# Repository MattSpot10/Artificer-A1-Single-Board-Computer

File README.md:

# Artificer A1 Single Board Computer
 An open source single board computer with AI capabilities. (Still in progress)

### **Features/Capabilites
- Alliwnner T527 SoC (Octa-core ARM Cortex-A55, up to 1.8 GHz)
- 4GB LPDDR4 SDRAM
- Dual Gigibit Ethernet (RJ45 ports capable of PoE)
- PCIe gen 2.1
- Display Port, HDMI, 2x4 lane MIPI DSI
- 4x2 lane MIPI CSI
- SD Card as boot media
- M8800DS2 Wifi/BT module with onboard PCB antenna
- 12V 5.5mm barrel jack power input
- 2x20 raspberry pi GPIO header
- 3.5mm sterio audio, mic
- 4xUSBA 2.0
- 1xUSBC 2.0 DRD

### **Progress/Plans (Since Jan 2025)**
**V1 Schematic capture**
- Done: Component choice, symbol, and footprint creation. Finished interconnects for Ethernet, USB, MIPI DSI & CSI, SDRAM, PCIe
- Todo: Interconnects for power, audio, gpio, I2C interfaces, wifi&bt, SD card.

**PCB Compatabilites**

The Allwinner T527 is a 0.5mm pitch BGA requiring these compatabilities for maufacturing:
- 3mil trace
- 3mil spacing
- 10.685mil pad
- 6mil drill
- 10.685mil pad - 6mil drill = 2.342mil anular ring
- 6 - 8 layers (Stackup and material not determined)

**Booting Linux**
- Add Spi flash chip to schematic for holding U Boot.
- Configure U Boot for loading the Linux kernel and the device tree blob.

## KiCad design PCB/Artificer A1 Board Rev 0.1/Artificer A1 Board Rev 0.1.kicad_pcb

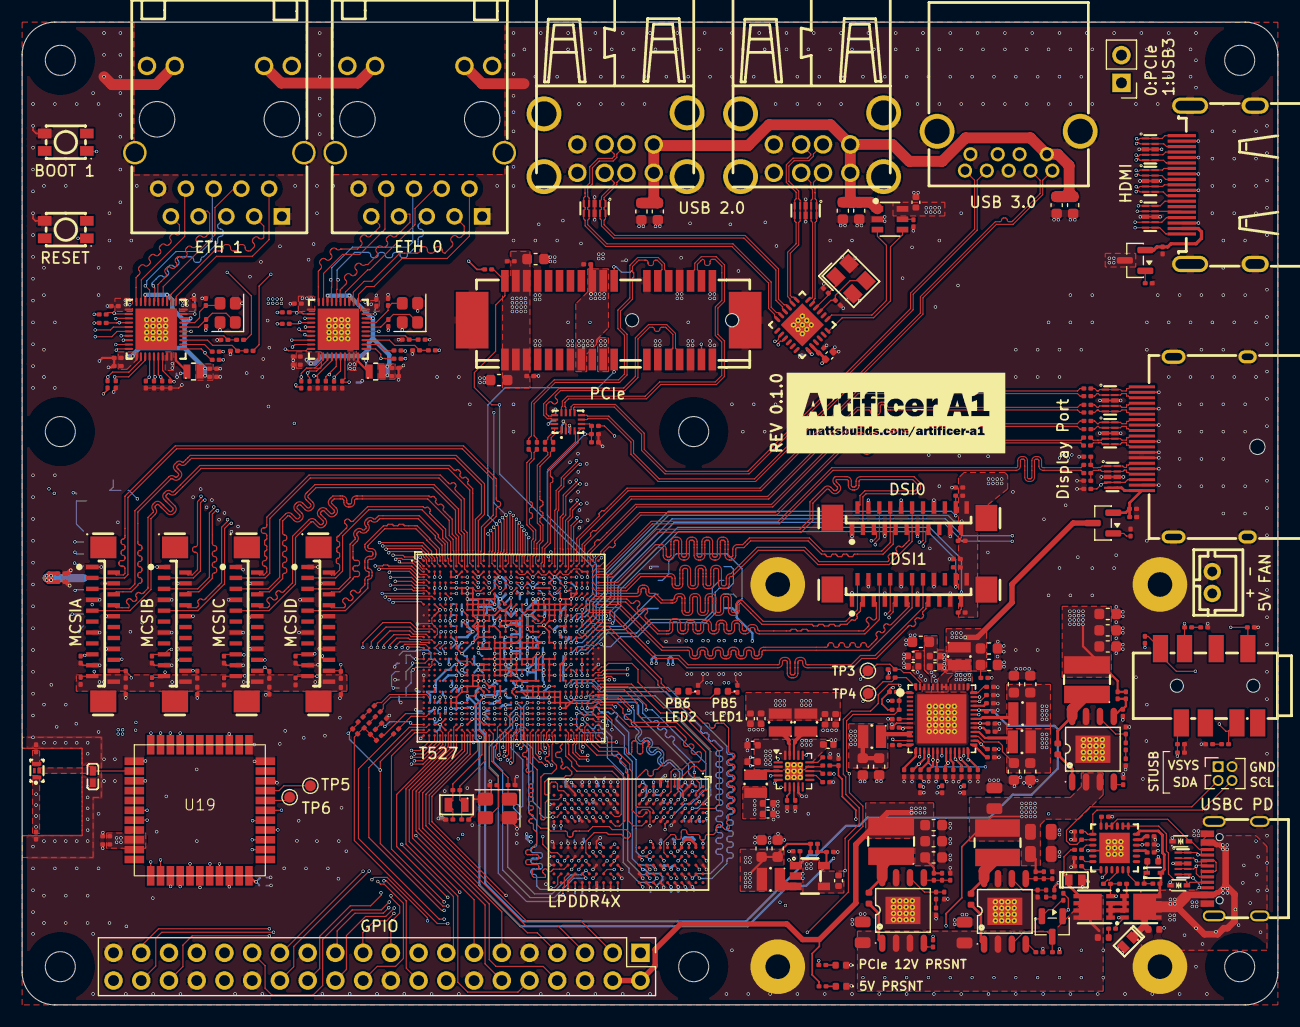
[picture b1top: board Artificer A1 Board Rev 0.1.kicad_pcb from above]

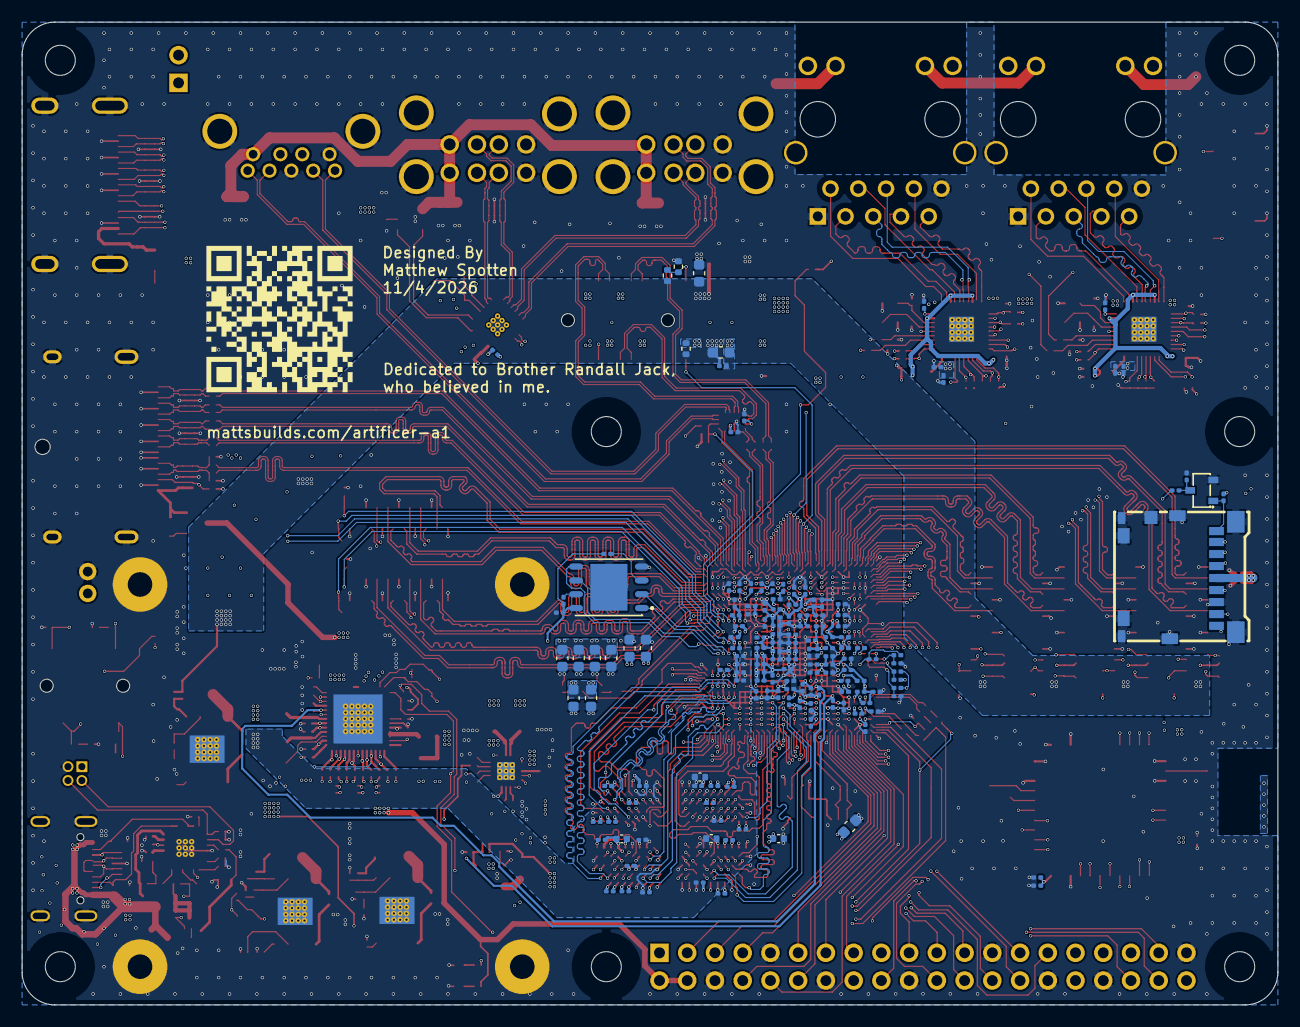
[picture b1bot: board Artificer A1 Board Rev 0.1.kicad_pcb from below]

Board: 6 copper layers, 115.0 x 90.0 mm, 510 parts (158 on the bottom side), 494 nets.

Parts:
C1, C14, C15: 10uF 50V; C_0805
C2, C9, C16, C17: 100nF 50V; C_0402
C3, C13: 1uF 25V; C_0402
C25, C27: 22uF 25V; C_0805
C85, C86, C87, C88, C133, C151, C154, C161, C309, C320, C321, C322, C323, C344, C345, C346, C347, C356, C358, C359, C360, C363, C364, C365, C375, C376, C383, C384, C392, C393, C398, C403, C406, C408, C410, C411, C412, C413, C414, C415, C416, C418, C419, C420, C421, C422, C423, C424, C426, C427, C428: 100nF 10V; C_0201_0603Metric
C134, C135, C136, C137, C138, C139, C140, C141, C142, C143, C158, C159, C160, C164, C165, C167, C168, C170, C171, C172, C173, C174, C175, C176, C177, C178, C181, C183, C184, C185, C186, C187, C189, C191, C193, C199, C200, C207, C208, C211, C212, C213, C214, C300, C301: 100nF 16V; C_0201_0603Metric
C162, C163: 10nF 10V; C_0201_0603Metric
C166, C169, C209, C210, C221, C222, C223, C224, C225, C226, C227, C228, C229, C230, C241, C253, C254, C255, C270, C271, C353: 2.2uF 10V; C_0201_0603Metric
C179, C180, C292, C293, C294, C295, C296, C297: 22uF 16V; C_0603_1608Metric
C182: 22pF 16V; C_0201_0603Metric
C188, C205, C291: 22pF 25V; C_0201_0603Metric
C190, C192, C194, C219, C220, C231, C232, C247, C248, C249, C250, C251, C252, C257, C267, C272: 1uF 10V; C_0201_0603Metric
C195, C197, C289: 3.3nF 16V; C_0201_0603Metric
C196, C204, C290: 47pF 16V; C_0201_0603Metric
C198: 33pF 50V; C_0201_0603Metric
C201: 1nF 16V; C_0201_0603Metric
C202: 33pF; C_0201_0603Metric
C215, C216, C217, C218: 6pF 16V; C_0201_0603Metric
C233, C234, C235, C236, C237, C238, C239, C240, C242, C261, C262, C263, C264, C265, C266, C268, C283, C284, C302, C303, C354, C377, C378, C385, C387, C389, C394, C399: 22uF 6.3V; C_0603_1608Metric
C243, C244, C245, C246, C256, C269, C273, C274, C275, C276, C277, C278, C324, C325, C326, C327: 10uF 6.3V; C_0402_1005Metric
C258: 1uF 6.3V; C_0402_1005Metric
C259, C260: 4pF 16V; C_0201_0603Metric
C279, C280, C281: 4.7uF 6.3V; C_0402_1005Metric
C282, C285, C286, C287, C288, C308, C310, C311, C312, C313, C314, C315, C316, C317, C318, C319, C328, C329, C330, C331, C332, C333, C334, C335, C336, C337, C341, C342, C348, C350, C351, C352, C379, C380, C381, C386, C388, C390, C391, C395, C396, C397, C400, C401, C402, C404, C405, C425: 2.2uF 6.3V; C_0201_0603Metric
C298: 6.2pF 16V; C_0201_0603Metric
C299: 0.4pF 16V; C_0201_0603Metric
C304, C305, C306, C307: 12pF 16V; C_0201_0603Metric
C338, C339, C340: 470nF 6.3V; C_0201_0603Metric
C374, C382, C407, C409, C417: 1uF 6.3V; C_0201_0603Metric
CN2: B2B-PH-K-S; CONN-TH_B2B-PH-K-S
CN3: PJ-393-8P_C49284725; AUDIO-TH_PJ-393-8P
Card1: TF-110; TF-SMD_TF-110
D1, D3: ESDA25P35-1U1M-ES; DFN1610-2L_L1.6-W1.0-P1.10-RD
D2: RED LED; LED_0402_1005Metric
D4, D5, D6, D7, D8, D9, D10, D11, D13: RClamp0524PATCT; SLP2510P8_L2.5-W1.0-P0.50-BL
D12, D14: LESD5D5.0CT1G_C5199850; SOD-523_L1.2-W0.8-LS1.6-BI
D15: B5819WT_C7502714; SOD-523_L1.2-W0.8-LS1.6-RD
D16, D17, D18: GREEN LED; LED_0402_1005Metric
DP1: CAR06-201EN5F; DP-SMD_CAR06-201EN5F
FPC1, FPC2: 0.5K-A-22PB; FPC-SMD_22P-P1.00_0.5K-A-22PB
H1, H2, H3, H4, H5, H6, H8: MountingHole; NP-mounting-hole
HDMI1: HD-A-05H9191N; HDMI-SMD_HD-A-05H9192N
J1: Conn_02x20_Odd_Even; PinHeader_2x20_P2.54mm_Vertical
J2: Conn_01x02; PinHeader_1x02_P2.54mm_Vertical
J3: Conn_02x02_Odd_Even; PinHeader_2x02_P1.27mm_Vertical
L2, L16: 3.3uH MTQH404020S3R3MBT; IND-SMD_L4.1-W4.1_MTQH404020S
L3, L4, L5, L6, L7, L8, L9, L10: APH252012C1R0MP01; IND-SMD_APH252012C3R3MP01
L11, L12: APH141208C2R2MP01; IND-SMD_L1.4-W1.2_AOTA-B141206SR47MT
L13: ANT162442DT-2001A2; ANT-SMD_6P-L1.6-W0.8-L
L14: MLG1005S1N3BT000; L0402
L15: 10uH MTQH404030S100MBT; IND-SMD_L4.1-W4.1_MTQH404030S
M1: Fan&Heatsink_40x40mm; custom_heatsink&fan_40x40mm
Q1, Q2: AON3419-TP; DFN-8_L3.0-W3.0-P0.65-BL
Q3, Q6, Q7: AO3401A; SOT-23
Q4: 2SK3018; SOT-23-3_L2.9-W1.4-P1.90-LS2.6-BR
R107, R108, R168, R176, R199, R202, R204, R205, R209, R212, R213, R214, R230, R231, R242: 10kΩ; R_0201_0603Metric
R109, R110, R111, R158, R162, R163, R164, R165, R166, R169, R170, R171, R172, R174, R184, R185, R195, R198: 100kΩ; R_0201_0603Metric
R112, R113: 2.49kΩ; R_0201_0603Metric
R114, R115, R116, R117, R118, R119, R120, R121, R122, R123, R124, R125, R126, R127, R128, R129, R130, R131, R132, R133, R134, R135, R136, R137, R215, R216, R217, R218, R219, R220, R221, R222, R223, R224, R225, R226, R227, R228: 4.7kΩ; R_0201_0603Metric
R144, R145, R146, R147, R156: 470Ω; R_0201_0603Metric
R148, R149, R150, R154, R157, R161, R173, R196, R197, R233, R234: 1kΩ; R_0201_0603Metric
R151, R152, R153: 200Ω; R_0201_0603Metric
R155: 39kΩ; R_0201_0603Metric
R159: 100Ω; R_0201_0603Metric
R160: 22kΩ; R_0201_0603Metric
R167, R175, R229, R232, R237, R241: 0Ω; R_0201_0603Metric
R177: 120Ω; R_0201_0603Metric
R178, R179: 240Ω; R_0201_0603Metric
R180: 18kΩ; R_0201_0603Metric
R181: 1.3kΩ; R_0201_0603Metric
R182, R189, R190: 200kΩ; R_0201_0603Metric
R183, R186, R191: 14kΩ; R_0201_0603Metric
R187: 75kΩ; R_0201_0603Metric
R188: 24kΩ; R_0201_0603Metric
R192: 27kΩ; R_0201_0603Metric
R193: 5.1kΩ; R_0201_0603Metric
R200: 10kΩ; R_0402_1005Metric
R201: 10k; R_0402_1005Metric
R203: 0Ω; R_0402_1005Metric
R206: 10MΩ; R_0201_0603Metric
R207: 4.3kΩ; R_0201_0603Metric
R208: 6.8kΩ; R_0201_0603Metric
R210, R211: 10k; R_0201_0603Metric
R235: 2kΩ; R_0201_0603Metric
R236: 47kΩ; R_0201_0603Metric
R238, R239: 22Ω; R_0201_0603Metric
R240: 1MΩ; R_0201_0603Metric
R243, R244, R245: 33kΩ; R_0201_0603Metric
RJ1, RJ2: HR911130A; RJ45-TH_HR911130A
SW1, SW2: TS-1185; SW-SMD_4P-L3.5-W3.0-P1.50-LS4.7
TP3, TP4: DCDC1; TestPoint_Pad_D1.0mm
TP5: BT-UART0_RX; TestPoint_Pad_D1.0mm
TP6: BT-UART0_TX; TestPoint_Pad_D1.0mm
U1: GT-USB-7010ASV; USB-C-SMD_G-SWITCH_GT-USB-7010ASV
U2: GD25LQ128EWIGR; WSON-8_L6.0-W5.0-P1.27-BL-EP
U3, U6: AP64500SP-13; SO-8_L4.9-W3.9-P1.27-LS6.0-BL-EP
U4: STUSB4500QTR; QFN-24_L4.0-W4.0-P0.50-BL-EP2.8
U5: AP64350SP-13; SO-8_L4.9-W3.9-P1.27-LS6.0-BL-EP
U8: T527M00X0DCH; BGA-664_L17.0-W17.0_T527
U9: SY8089A1AAC; TSOT-23-5_L2.9-W1.6-P0.95-LS2.8-BR
U10: AXP717B; QFN-52_L6.0-W6.0-P0.40-TL-EP4.5
U11: AXP323
U12: K4UBE3D4AB-MGCL; FBGA-200_L14.5-W10.0_RS1G32LF4D2BDS-53BT
U13, U24, U25, U26: AFC11-S22ICA-00; FPC-SMD_22P-P1.00_AFC11-S22ICC-00
U14, U15: RTL8211F-CG; WQFN-40_L5.0-W5.0-P0.4-BL-EP
U16: HD3SS3202IRSVR; UQFN-16_L2.6-W1.8-P0.40-BL
U17: X1618WVS-36-9TV15; CONN-SMD_X3113WVS-36-9TV01
U19: M8800DS2-40
U21: CH217K; SOT-23-6_L2.9-W1.6-P0.95-LS2.8-BL
U22: CH334F_C5187527; QFN-24_L4.0-W4.0-P0.50-BL-EP2.8
USB1, USB2: Double layer DIP 90° black; USB-A-TH_USB-M-51
USB4: HC-USB3.0-L168-WJ; USB-3.0-A-TH_HC-USB3.0-L168-WJ
X1, X2: 25MHz; Crystal_SMD_2520-4Pin_2.5x2.0mm
X3: SMD-3225_4P12M12PF10PPM; CRYSTAL-SMD_4P-L3.2-W2.5-BL
X4: 25MHz; Crystal_SMD_3225-4Pin_3.2x2.5mm
X5: SC-20S32.768kHz20PPM9pF; OSC-SMD_L2.0-W1.2

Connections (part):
5V_SYS: C231.2, C232.2, C245.2, C246.2, C247.2, C251.2, C252.2, C257.2, C258.2, C267.2, C291.2, C295.2, C296.2, C297.2, CN2.1, J1.2, J1.4, L16.2, Q3.2 (S), Q6.3 (D), R184.1, R192.2, R243.2, U10.9 (VIN1), U10.15 (ALDOIN), U10.20 (BLDOIN), U10.25 (CLDOIN), U10.31 (VIN3), U10.32 (VIN2), U10.49 (VBUS_1), U10.50 (VBUS_2), U21.6 (VIN), U22.19 (V5)
323-ALDO1: C241.2, U11.15 (ALDO1)
323-DCDC1/2: C275.2, C276.2, C277.2, C278.2, C282.2, C283.2, C284.2, C285.2, C286.2, C374.2, C375.2, C376.2, L8.2, L9.2, U8.T19 (VDDCPUB), U8.T21 (VDDCPUB), U8.T22 (VDDCPUB), U8.U18 (VDDCPUB), U8.U19 (VDDCPUB), U8.U21 (VDDCPUB), U8.U22 (VDDCPUB)
323-DCDC3: C273.2, C274.2, C399.2, C400.2, C401.2, C402.2, C403.2, C404.2, L10.2, U8.AA12 (VDDDNR), U8.AA13 (VDDDNR), U8.Y12 (VDDDNR), U8.Y13 (VDDDNR)
323-DLDO1: C270.2, U11.12 (DLDO1)
323-RTCLDO: C271.2, U11.7 (RTCLDO)
+12V: C15.1, C25.1, C27.1, C172.2, C178.2, C179.2, C180.2, C188.2, L15.2, R180.2, R242.2, U6.2 (VIN), U6.3 (EN), U17.2 (A2_+12V), U17.3 (A3_+12V), U17.19 (B1_+12V), U17.20 (B2_+12V), U17.21 (B3_+12V)
/ETH0.RGMII-CLKIN: U8.C17 (PH3), U14.35 (CLKOUT)
/ETH0.RGMII-INTB: R126.2, U8.B15 (PH13), U14.31 (INTB/PMEB)
/ETH0.RGMII-MDC: U8.C16 (PH9), U14.13 (MDC)
/ETH0.RGMII-MDIO: R130.2, U8.B16 (PH10), U14.14 (MDIO)
/ETH0.RGMII-PHYRSTB: R128.2, U8.D16 (PH8), U14.12 (PHYRSTB)
/ETH0.RGMII-RXCK: R116.1, U8.B14 (PH16), U14.27 (PHYAD1/RXC)
/ETH0.RGMII-RXCTL: R118.1, U8.D18 (PH2), U14.26 (PHYAD2/RXCTL)
/ETH0.RGMII-RXD0: R134.1, U8.E18 (PH1), U14.25 (RXDLY/RXD0)
/ETH0.RGMII-RXD1: R132.1, U8.F18 (PH0), U14.24 (TXDLY/RXD1)
/ETH0.RGMII-RXD2: R136.1, U8.D14 (PH15), U14.23 (PLLOFF/RXD2)
/ETH0.RGMII-RXD3: R114.2, U8.E14 (PH14), U14.22 (PHYAD0/RXD3)
/ETH0.RGMII-TXCK: U8.G12 (PH6), U14.20 (TXC)
/ETH0.RGMII-TXCTL: U8.F14 (PH7), U14.19 (TXCTL)
/ETH0.RGMII-TXD0: U8.E16 (PH5), U14.18 (TXD0)
/ETH0.RGMII-TXD1: U8.B17 (PH4), U14.17 (TXD1)
/ETH0.RGMII-TXD2: U8.A14 (PH18), U14.16 (TXD2)
/ETH0.RGMII-TXD3: U8.B13 (PH17), U14.15 (TXD3)
/ETH1.RGMII-CLKIN: U8.E2 (PJ3), U15.35 (CLKOUT)
/ETH1.RGMII-INTB: R127.2, U8.J1 (PJ16), U15.31 (INTB/PMEB)
/ETH1.RGMII-MDC: U8.H2 (PJ8), U15.13 (MDC)
/ETH1.RGMII-MDIO: R131.2, U8.H3 (PJ9), U15.14 (MDIO)
/ETH1.RGMII-PHYRSTB: R129.2, U8.G4 (PJ10), U15.12 (PHYRSTB)
/ETH1.RGMII-RXCK: R117.1, U8.J5 (PJ13), U15.27 (PHYAD1/RXC)
/ETH1.RGMII-RXCTL: R119.1, U8.E1 (PJ2), U15.26 (PHYAD2/RXCTL)
/ETH1.RGMII-RXD0: R135.1, U8.D2 (PJ1), U15.25 (RXDLY/RXD0)
/ETH1.RGMII-RXD1: R133.1, U8.D1 (PJ0), U15.24 (TXDLY/RXD1)
/ETH1.RGMII-RXD2: R137.1, U8.J4 (PJ12), U15.23 (PLLOFF/RXD2)
/ETH1.RGMII-RXD3: R115.2, U8.G5 (PJ11), U15.22 (PHYAD0/RXD3)
/ETH1.RGMII-TXCK: U8.G1 (PJ6), U15.20 (TXC)
/ETH1.RGMII-TXCTL: U8.G2 (PJ7), U15.19 (TXCTL)
/ETH1.RGMII-TXD0: U8.F2 (PJ5), U15.18 (TXD0)
/ETH1.RGMII-TXD1: U8.F1 (PJ4), U15.17 (TXD1)
/ETH1.RGMII-TXD2: U8.L5 (PJ15), U15.16 (TXD2)
/ETH1.RGMII-TXD3: U8.L4 (PJ14), U15.15 (TXD3)
/T527/AP-WAKE-BT: U8.AN2 (PM1), U19.6 (HOST_WAKE_BT)
/T527/AP-WAKE-WL: U8.AM4 (PM2), U19.24 (HOST_WAKE_WL)
/T527/BOOT_SEL_ADC: R207.2, R208.1, U8.W1 (GPADC0)
/T527/BT-PCM-CLK: U8.U4 (PG11), U19.26 (PCM_CLK)
/T527/BT-PCM-DIN: U8.U1 (PG14), U19.25 (PCM_DOUT)
/T527/BT-PCM-DOUT: U8.U2 (PG13), U19.27 (PCM_DIN)
/T527/BT-PCM-SYNC: U8.U3 (PG12), U19.28 (PCM_FSYNC)
/T527/BT-UART-CTS: U8.U6 (PG9), U19.41 (UART1_RTS)
/T527/BT-UART-RTS: U8.R4 (PG8), U19.44 (UART1_CTS)
/T527/BT-UART-RX: U8.R5 (PG7), U19.42 (UART1_TX)
/T527/BT-UART-TX: U8.R6 (PG6), U19.43 (UART1_RX)
/T527/BT-WAKE-AP: U8.AN3 (PM0), U19.7 (BT_WAKE_HOST)
/T527/DBG_DN: D13.4 (IN3), D13.7 (NC), U1.A7 (DN1), U1.B7 (DN2), U8.B24 (USB0-DM)
/T527/DBG_DP: D13.2 (IN2), D13.9 (NC), U1.A6 (DP1), U1.B6 (DP2), U8.A24 (USB0-DP)
/T527/DBG_UART0_RX: D13.5 (IN4), D13.6 (NC), U1.B8 (SBU2), U8.R29 (PB10)
/T527/DBG_UART0_TX: D13.1 (IN1), D13.10 (NC), U1.A8 (SBU1), U8.R28 (PB9)
/T527/DDR-PARA-SEL-ADC1: R209.1, R210.2, U8.W2 (GPADC1)
/T527/DDR-PARA-SEL-ADC2: R211.2, R212.1, U8.W3 (GPADC2)
/T527/DSI0-CKN: FPC1.8, U8.E33 (PD5)
/T527/DSI0-CKP: FPC1.9, U8.E32 (PD4)
/T527/DSI0-D0N: FPC1.2, U8.D33 (PD1)
/T527/DSI0-D0P: FPC1.3, U8.D32 (PD0)
/T527/DSI0-D1N: FPC1.5, U8.E31 (PD3)
/T527/DSI0-D1P: FPC1.6, U8.E30 (PD2)
/T527/DSI0-D2N: FPC1.11, U8.F33 (PD7)
/T527/DSI0-D2P: FPC1.12, U8.F32 (PD6)
/T527/DSI0-D3N: FPC1.14, U8.G31 (PD9)
/T527/DSI0-D3P: FPC1.15, U8.G30 (PD8)
/T527/DSI1-CKN: FPC2.8, U8.J30 (PD15)
/T527/DSI1-CKP: FPC2.9, U8.J29 (PD14)
/T527/DSI1-D0N: FPC2.2, U8.G33 (PD11)
/T527/DSI1-D0P: FPC2.3, U8.G32 (PD10)
/T527/DSI1-D1N: FPC2.5, U8.H32 (PD13)
/T527/DSI1-D1P: FPC2.6, U8.H31 (PD12)
/T527/DSI1-D2N: FPC2.11, U8.J33 (PD17)
/T527/DSI1-D2P: FPC2.12, U8.J32 (PD16)
/T527/DSI1-D3N: FPC2.14, U8.K32 (PD19)
/T527/DSI1-D3P: FPC2.15, U8.K31 (PD18)
/T527/DXIN: C304.2, U8.AM13 (DXIN), X4.1
/T527/DXOUT: C305.2, U8.AN13 (DXOUT), X4.3
/T527/Disp0-SCL: FPC1.20, R223.2, U8.R30 (PB11)
/T527/Disp0-SDA: FPC1.21, R224.2, U8.R31 (PB12)
/T527/Disp1-SCL: FPC2.20, R225.2, U8.L31 (PD22)
/T527/Disp1-SDA: FPC2.21, R226.2, U8.L32 (PD23)
/T527/EDP-AUXN: C208.1, U8.C33 (EDPAUXN)
/T527/EDP-AUXP: C207.1, U8.C32 (EDPAUXP)
/T527/EDP-HPD: D9.4 (IN3), D9.7 (NC), DP1.18 (HOT_PLUG), R109.1, U8.C29 (EDPHPD)
/T527/EDP-TX0N: C135.1, U8.B29 (EDPTX0N)
/T527/EDP-TX0P: C134.1, U8.A29 (EDPTX0P)
/T527/EDP-TX1N: C137.1, U8.B30 (EDPTX1N)
/T527/EDP-TX1P: C136.1, U8.A30 (EDPTX1P)
/T527/EDP-TX2N: C139.1, U8.B31 (EDPTX2N)
/T527/EDP-TX2P: C138.1, U8.A31 (EDPTX2P)
/T527/EDP-TX3N: C141.1, U8.B33 (EDPTX3N)
/T527/EDP-TX3P: C140.1, U8.B32 (EDPTX3P)
/T527/FEL: SW1.1, U8.F16 (FEL)
/T527/HBIAS: C353.2, R235.1, U8.AL1 (HBIAS)
/T527/HCEC: D6.1 (IN1), D6.10 (NC), HDMI1.13 (CEC), U8.E28 (HCEC)
/T527/HHPD: D6.5 (IN4), D6.6 (NC), HDMI1.19 (HOT_PLUG_DET), U8.D28 (HHPD)
/T527/HP-DET: R236.2, U8.AJ2 (HPDET)
/T527/HPOUTFB: C198.1, C202.2, CN3.4, R234.1, R237.1, U8.AM1 (HPOUTFB)
/T527/HPOUTL: C174.2, CN3.6, U8.AL2 (HPOUTL)
/T527/HPOUTR: C175.2, CN3.3, U8.AM2 (HPOUTR)
/T527/HS-MIC: C198.2, C201.2, CN3.1, R154.2, R233.1, R235.2
/T527/HSCL: D6.2 (IN2), D6.9 (NC), HDMI1.15 (I2C-CLK), U8.D26 (HSCL)
/T527/HSDA: D6.4 (IN3), D6.7 (NC), HDMI1.16 (I2C_DATA), U8.E26 (HSDA)
/T527/HTX0N: D5.2 (IN2), D5.9 (NC), HDMI1.9 (D0-), U8.C27 (HTX0N)
/T527/HTX0P: D5.1 (IN1), D5.10 (NC), HDMI1.7 (D0+), U8.B27 (HTX0P)
/T527/HTX1N: D4.5 (IN4), D4.6 (NC), HDMI1.6 (D1-), U8.B26 (HTX1N)
/T527/HTX1P: D4.4 (IN3), D4.7 (NC), HDMI1.4 (D1+), U8.A26 (HTX1P)
/T527/HTX2N: D4.2 (IN2), D4.9 (NC), HDMI1.3 (D2-), U8.C25 (HTX2N)
/T527/HTX2P: D4.1 (IN1), D4.10 (NC), HDMI1.1 (D2+), U8.B25 (HTX2P)
/T527/HTXCN: D5.5 (IN4), D5.6 (NC), HDMI1.12 (CK-), U8.B28 (HTXCN)
/T527/HTXCP: D5.4 (IN3), D5.7 (NC), HDMI1.10 (CK+), U8.A28 (HTXCP)
/T527/LED1: D17.2 (A), U8.N32 (PB5)
/T527/LED2: D18.2 (A), U8.N33 (PB6)
/T527/LED-EN-A: U8.J7 (PE11), U13.18
/T527/LED-EN-B: U8.A2 (PE7), U24.18
/T527/LED-EN-C: U8.A3 (PE6), U25.18
/T527/LED-EN-D: U8.B1 (PE9), U26.18
/T527/MCSIA-CKN: U8.A10 (PK4), U13.8
/T527/MCSIA-CKP: U8.B10 (PK5), U13.9
/T527/MCSIA-D0N: U8.A12 (PK0), U13.2
/T527/MCSIA-D0P: U8.B12 (PK1), U13.3
/T527/MCSIA-D1N: U8.B11 (PK2), U13.5
/T527/MCSIA-D1P: U8.C11 (PK3), U13.6
/T527/MCSIB-CKN: U8.E8 (PK10), U24.8
/T527/MCSIB-CKP: U8.D8 (PK11), U24.9
/T527/MCSIB-D0N: U8.E12 (PK6), U24.2
/T527/MCSIB-D0P: U8.D12 (PK7), U24.3
/T527/MCSIB-D1N: U8.E10 (PK8), U24.5
/T527/MCSIB-D1P: U8.D10 (PK9), U24.6
/T527/MCSIC-CKN: U8.B7 (PK16), U25.8
/T527/MCSIC-CKP: U8.C7 (PK17), U25.9
/T527/MCSIC-D0N: U8.B9 (PK12), U25.2
/T527/MCSIC-D0P: U8.C9 (PK13), U25.3
/T527/MCSIC-D1N: U8.A8 (PK14), U25.5
/T527/MCSIC-D1P: U8.B8 (PK15), U25.6
/T527/MCSID-CKN: U8.A4 (PK22), U26.8
/T527/MCSID-CKP: U8.B4 (PK23), U26.9
/T527/MCSID-D0N: U8.A6 (PK18), U26.2
/T527/MCSID-D0P: U8.B6 (PK19), U26.3
/T527/MCSID-D1N: U8.A5 (PK20), U26.5
/T527/MCSID-D1P: U8.B5 (PK21), U26.6
/T527/MICIN3N: C199.2, U8.AF1 (MICIN3N)
/T527/MICIN3P: C200.2, U8.AF2 (MICIN3P)
/T527/PCIE0-CLKREQN: U8.C13 (PH19), U17.35 (B17_PRSNT#2)
/T527/PCIE0-PERSTN: R200.2, R201.2, U8.A16 (PH11), U17.11 (A11_PCIeRST)
/T527/PCIE0-WAKEN: U8.C15 (PH12), U17.29 (B11_WAKE#)
/T527/PCIE-CARD-PRESENT: R202.2, U8.L28 (PD20), U17.1 (A1_PRSNT#1)
/T527/PCIE-CLKN: C85.2, U8.C21 (PCIEREFCLKN)
/T527/PCIE-CLKP: C86.2, U8.B21 (PCIEREFCLKP)
/T527/PCIE-DN: C87.2, U8.B22 (PCIETX0-DN/USB)
/T527/PCIE-DP: C88.2, U8.A22 (PCIETX0-DP/USB)
/T527/PCIE-REF-CLKN: C85.1, U17.14 (A14_REFCLK-)
/T527/PCIE-REF-CLKP: C86.1, U17.13 (A13_REF_CLK+)
/T527/PCIE-RX0-DN: U8.C23 (PCIERX0-DN/US), U16.4 (A1p)
/T527/PCIE-RX0-DP: U8.B23 (PCIERX0-DP/US), U16.5 (A1n)
/T527/PCIE-SEL: C301.2, R197.1, R198.2, U8.L29 (PD21), U16.6 (SEL)
/T527/PCIE-TX0-DN: C87.1, U16.16 (A0p)
/T527/PCIE-TX0-DP: C88.1, U16.1 (A0n)
/T527/PI0: J1.18, U8.AH13 (PI0)
/T527/PI1: J1.22, U8.AG13 (PI1)
/T527/PI2: J1.24, U8.AL15 (PI2)
/T527/PI3: J1.23, U8.AN15 (PI3)
/T527/PI4: J1.19, U8.AM15 (PI4)
/T527/PI5: J1.21, U8.AJ15 (PI5)
/T527/PI6: J1.26, U8.AK15 (PI6)
/T527/PI7: J1.40, U8.AH15 (PI7)
/T527/PI8: J1.38, U8.AL16 (PI8)
/T527/PI9: J1.29, U8.AM16 (PI9)
/T527/PI10: J1.31, U8.AN17 (PI10)
/T527/PI11: J1.33, U8.AM17 (PI11)
/T527/PI12: J1.35, U8.AL17 (PI12)
/T527/PI13: J1.37, U8.AK17 (PI13)
/T527/PI14: J1.32, U8.AM18 (PI14)
/T527/PI15: J1.36, U8.AH17 (PI15)
/T527/PL2: J1.8, U8.AN7 (PL2)
/T527/PL3: J1.10, U8.AM6 (PL3)
/T527/PL5: J1.13, U8.AL7 (PL5)
/T527/PL6: J1.11, U8.AN8 (PL6)
/T527/PL7: J1.7, U8.AM8 (PL7)
/T527/PL8: J1.5, U8.AN9 (PL8)
/T527/PL9: J1.3, U8.AM9 (PL9)
/T527/PL10: J1.12, U8.AK9 (PL10)
/T527/PL11: J1.15, U8.AJ9 (PL11)
/T527/PL12: J1.28, U8.AK7 (PL12)
/T527/PL13: J1.27, U8.AJ7 (PL13)
/T527/PMU-SCK: R227.2, TP4.1 (1_1), U8.AN6 (PL0), U10.52 (SCK), U11.5 (SDA)
/T527/PMU-SDA: R228.2, TP3.1 (1_1), U8.AN5 (PL1), U10.51 (SDA), U11.6 (SCL)
/T527/POWER-EN-A: R169.2, U8.C2 (PE10), U13.17
/T527/POWER-EN-B: R170.2, U8.E6 (PE0), U24.17
/T527/POWER-EN-C: R171.2, U8.B3 (PE5), U25.17
/T527/POWER-EN-D: R172.2, U8.B2 (PE8), U26.17
/T527/PWR-EN: U8.AN4 (PM4), U19.12 (PWR_KEY)
/T527/SCL-A: R216.2, U8.C1 (PE12), U13.20
/T527/SCL-B: R218.2, U8.C4 (PE1), U24.20
/T527/SCL-C: R220.2, U8.E4 (PE3), U25.20
/T527/SCL-D: R222.2, U8.L7 (PE14), U26.20
/T527/SDA-A: R215.2, U8.G6 (PE13), U13.21
/T527/SDA-B: R217.2, U8.E5 (PE2), U24.21
/T527/SDA-C: R219.2, U8.C3 (PE4), U25.21
/T527/SDA-D: R221.2, U8.N7 (PE15), U26.21
/T527/SDC0-CLK: Card1.5 (CLK), U8.C19 (PF2)
/T527/SDC0-CMD: Card1.3 (CMD), U8.B19 (PF3)
/T527/SDC0-D0: Card1.7 (DAT0), U8.A20 (PF1)
/T527/SDC0-D1: Card1.8 (DAT1), U8.B20 (PF0)
/T527/SDC0-D2: Card1.1 (DAT2), U8.A18 (PF5)
/T527/SDC0-D3: Card1.2 (CD/DAT3), U8.B18 (PF4)
/T527/SDC0-DET: R196.2, U8.D20 (PF6)
/T527/SDC1-CLK: U8.R1 (PG0), U19.17 (SD_CLK)
/T527/SDC1-CMD: U8.R2 (PG1), U19.16 (SD_CMD)
/T527/SDC1-D0: U8.P3 (PG2), U19.18 (SD_D0)
/T527/SDC1-D1: U8.P2 (PG3), U19.19 (SD_D1)
/T527/SDC1-D2: U8.T3 (PG4), U19.14 (SD_D2)
/T527/SDC1-D3: U8.T2 (PG5), U19.15 (SD_D3)
/T527/SPI0_CLK: U2.6 (SCLK), U8.V31 (PC11)
/T527/SPI0_CS: U2.1 (~CS), U8.U29 (PC3)
/T527/SPI0_DI: U2.2 (SO(IO1)), U8.U28 (PC4)
/T527/SPI0_DO: U2.5 (SI(IO0)), U8.U30 (PC2)
/T527/SPI0_HOLD: R204.2, U2.7 (HOLD#(IO3))
/T527/SPI0_WP: R205.2, U2.3 (WP#(IO2))
/T527/USB1-DN: U8.E24 (USB1-DM), U22.14 (DMU)
/T527/USB1-DP: U8.D24 (USB1-DP), U22.15 (DPU)
/T527/USB2-DN: U8.E22 (USB2-DM), USB4.2 (D-)
/T527/USB2-DP: U8.D22 (USB2-DP), USB4.3 (D+)
/T527/VRA1: C338.2, U8.AG5 (VRA1)
/T527/VRA2: C339.2, U8.AG4 (VRA2)
/T527/VRP: C340.2, U8.AC7 (VRP)
/T527/WL-WAKE-AP: U8.AM3 (PM3), U19.13 (WL_HOST_WAKE)
/T527/X32KIN: C306.2, R206.1, U8.AM12 (X32KIN), X5.1 (OSC1)
/T527/X32KOUT: C307.2, R206.2, U8.AM11 (X32KOUT), X5.2 (OSC2)
/display/AUX_CH_N: C208.2, D9.2 (IN2), D9.9 (NC), DP1.17 (AUX_CH_N), R108.1
/display/AUX_CH_P: C207.2, D9.1 (IN1), D9.10 (NC), DP1.15 (AUX_CH_P), R107.1
/display/ML_LANE0_N: C135.2, D7.2 (IN2), D7.9 (NC), DP1.3 (ML_LANE0_N)
/display/ML_LANE0_P: C134.2, D7.1 (IN1), D7.10 (NC), DP1.1 (ML_LANE0_P)
/display/ML_LANE1_N: C137.2, D7.5 (IN4), D7.6 (NC), DP1.6 (ML_LANE1_N)
/display/ML_LANE1_P: C136.2, D7.4 (IN3), D7.7 (NC), DP1.4 (ML_LANE1_P)
/display/ML_LANE2_N: C139.2, D8.2 (IN2), D8.9 (NC), DP1.9 (ML_LANE2_N)
/display/ML_LANE2_P: C138.2, D8.1 (IN1), D8.10 (NC), DP1.7 (ML_LANE2_P)
/display/ML_LANE3_N: C141.2, D8.5 (IN4), D8.6 (NC), DP1.12 (ML_LANE3_N)
/display/ML_LANE3_P: C140.2, D8.4 (IN3), D8.7 (NC), DP1.10 (ML_LANE3_P)
/dram/SAA0: U8.AJ33 (SA2), U12.H2 (CA0_a)
/dram/SAA1: U8.AJ32 (SA11), U12.J2 (CA1_a)
/dram/SAA2: U8.AG30 (SA1), U12.H9 (CA2_a)
/dram/SAA3: U8.AG29 (SA10), U12.H10 (CA3_a)
/dram/SAA4: U8.AJ30 (SA17), U12.H11 (CA4_a)
/dram/SAA5: U8.AJ31 (SA9), U12.J11 (CA5_a)
/dram/SAB0: U8.AJ25 (SBA1), U12.R2 (CA0_b)
/dram/SAB1: U8.AH25 (SA4), U12.P2 (CA1_b)
/dram/SAB2: U8.AL25 (SA8), U12.R9 (CA2_b)
/dram/SAB3: U8.AK25 (SBA0), U12.R10 (CA3_b)
/dram/SAB4: U8.AJ27 (SA16), U12.R11 (CA4_b)
/dram/SAB5: U8.AL29 (SACT), U12.P11 (CA5_b)
/dram/SCKA-N: U8.AN30 (SCKN), U12.J9 (CK_c_a)
/dram/SCKA-P: U8.AM30 (SCKP), U12.J8 (CK_t_a)
/dram/SCKB-N: U8.AN29 (SA15), U12.P9 (CK_c_b)
/dram/SCKB-P: U8.AM28 (SA14), U12.P8 (CK_t_b)
/dram/SCKE0-A: U8.AM31 (SCKE0), U12.J4 (CKE0_a)
/dram/SCKE0-B: U8.AN27 (SA6), U12.P4 (CKE0_b)
/dram/SCKE1-A: U8.AL31 (SA12), U12.J5 (CKE1_a)
/dram/SCKE1-B: U8.AM27 (SBG1), U12.P5 (CKE1_b)
/dram/SCS0-A: U8.AN32 (SCS0), U12.H4 (CS0_a)
/dram/SCS0-B: U8.AK29 (SA13), U12.R4 (CS0_b)
/dram/SCS1-A: U8.AM32 (SCS1), U12.H3 (CS1_a)
/dram/SCS1-B: U8.AK27 (SA5), U12.R3 (CS1_b)
/dram/SDQ0: U8.AE28 (SDQ0), U12.B2 (DQ0_a)
/dram/SDQ1: U8.AE27 (SDQ1), U12.C2 (DQ1_a)
/dram/SDQ2: U8.AG32 (SDQ2), U12.E2 (DQ2_a)
/dram/SDQ3: U8.AH33 (SDQ3), U12.F2 (DQ3_a)
/dram/SDQ4: U8.AE30 (SDQ4), U12.F4 (DQ4_a)
/dram/SDQ5: U8.AD32 (SDQ5), U12.E4 (DQ5_a)
/dram/SDQ6: U8.AE31 (SDQ6), U12.C4 (DQ6_a)
/dram/SDQ7: U8.AD33 (SDQ7), U12.B4 (DQ7_a)
/dram/SDQ8: U8.AC27 (SDQ8), U12.B11 (DQ8_a)
/dram/SDQ9: U8.AC28 (SDQ9), U12.C11 (DQ9_a)
/dram/SDQ10: U8.AC30 (SDQ10), U12.E11 (DQ10_a)
/dram/SDQ11: U8.AC31 (SDQ11), U12.F11 (DQ11_a)
/dram/SDQ12: U8.AA33 (SDQ12), U12.F9 (DQ12_a)
/dram/SDQ13: U8.AA31 (SDQ13), U12.E9 (DQ13_a)
/dram/SDQ14: U8.AA28 (SDQ14), U12.C9 (DQ14_a)
/dram/SDQ15: U8.AA27 (SDQ15), U12.B9 (DQ15_a)
/dram/SDQ16: U8.AM25 (SDQ16), U12.AA2 (DQ0_b)
/dram/SDQ17: U8.AN25 (SDQ17), U12.Y2 (DQ1_b)
/dram/SDQ18: U8.AH23 (SDQ18), U12.V2 (DQ2_b)
/dram/SDQ19: U8.AK23 (SDQ19), U12.U2 (DQ3_b)
/dram/SDQ20: U8.AL23 (SDQ20), U12.U4 (DQ4_b)
/dram/SDQ21: U8.AM22 (SDQ21), U12.V4 (DQ5_b)
/dram/SDQ22: U8.AN21 (SDQ22), U12.Y4 (DQ6_b)
/dram/SDQ23: U8.AG21 (SDQ23), U12.AA4 (DQ7_b)
/dram/SDQ24: U8.AG19 (SDQ24), U12.AA11 (DQ8_b)
/dram/SDQ25: U8.AH19 (SDQ25), U12.Y11 (DQ9_b)
/dram/SDQ26: U8.AK19 (SDQ26), U12.V11 (DQ10_b)
/dram/SDQ27: U8.AL19 (SDQ27), U12.U11 (DQ11_b)
/dram/SDQ28: U8.AM21 (SDQ28), U12.U9 (DQ12_b)
/dram/SDQ29: U8.AL21 (SDQ29), U12.V9 (DQ13_b)
/dram/SDQ30: U8.AK21 (SDQ30), U12.Y9 (DQ14_b)
/dram/SDQ31: U8.AH21 (SDQ31), U12.AA9 (DQ15_b)
/dram/SDQM0: U8.AE33 (SDQM0), U12.C3 (DMI0_a)
/dram/SDQM1: U8.AC32 (SDQM1), U12.C10 (DMI1_a)
/dram/SDQM2: U8.AM24 (SDQM2), U12.Y3 (DMI0_b)
/dram/SDQM3: U8.AN20 (SDQM3), U12.Y10 (DMI1_b)
/dram/SDQS0N: U8.AF33 (SDQS0N), U12.E3 (DQS0_c_a)
/dram/SDQS0P: U8.AF32 (SDQS0P), U12.D3 (DQS0_t_a)
/dram/SDQS1N: U8.AB33 (SDQS1N), U12.E10 (DQS1_c_a)
/dram/SDQS1P: U8.AB32 (SDQS1P), U12.D10 (DQS1_t_a)
/dram/SDQS2N: U8.AN23 (SDQS2N), U12.V3 (DQS0_c_b)
/dram/SDQS2P: U8.AM23 (SDQS2P), U12.W3 (DQS0_t_b)
/dram/SDQS3N: U8.AN19 (SDQS3N), U12.V10 (DQS1_c_b)
/dram/SDQS3P: U8.AM19 (SDQS3P), U12.W10 (DQS1_t_b)
/dram/SRST: U8.AG23 (SRST), U12.T11 (RESET_n)
/ethernet0/GM_LED0: R120.2, U14.32 (CFG_EXT/LED0)
/ethernet0/GM_LED1: R122.1, R144.2, U14.33 (CFG_LDO0/LED1)
/ethernet0/GM_LED2: R124.1, R146.2, U14.34 (CFG_LDO1/LED2)
/ethernet0/GM_MDI0N: RJ1.P3 (MDI0-), U14.2 (MDIN0)
/ethernet0/GM_MDI0P: RJ1.P2 (MDI0+), U14.1 (MDIP0)
/ethernet0/GM_MDI1N: RJ1.P7 (MDI1-), U14.5 (MDIN1)
/ethernet0/GM_MDI1P: RJ1.P4 (MDI1+), U14.4 (MDIP1)
/ethernet0/GM_MDI2N: RJ1.P6 (MDI2-), U14.7 (MDIN2)
/ethernet0/GM_MDI2P: RJ1.P5 (MDI2+), U14.6 (MDIP2)
/ethernet0/GM_MDI3N: RJ1.P9 (MDI3-), U14.10 (MDIN3)
/ethernet0/GM_MDI3P: RJ1.P8 (MDI3+), U14.9 (MDIP3)
/ethernet0/GM_VDD10: C160.2, C166.2, C211.2, C213.2, L11.2, U14.3 (AVDD10), U14.8 (AVDD10), U14.21 (DVDD10), U14.38 (AVDD10)
/ethernet0/GM_XTAL_IN: C215.2, U14.36 (XTAL_IN), X1.1
/ethernet0/GM_XTAL_OUT: C217.2, U14.37 (XTAL_OUT/EXT_CLK), X1.3
/ethernet 1/GM_LED0: R121.2, U15.32 (CFG_EXT/LED0)
/ethernet 1/GM_LED1: R123.1, R145.2, U15.33 (CFG_LDO0/LED1)
/ethernet 1/GM_LED2: R125.1, R147.2, U15.34 (CFG_LDO1/LED2)
/ethernet 1/GM_MDI0N: RJ2.P3 (MDI0-), U15.2 (MDIN0)
/ethernet 1/GM_MDI0P: RJ2.P2 (MDI0+), U15.1 (MDIP0)
/ethernet 1/GM_MDI1N: RJ2.P7 (MDI1-), U15.5 (MDIN1)
/ethernet 1/GM_MDI1P: RJ2.P4 (MDI1+), U15.4 (MDIP1)
/ethernet 1/GM_MDI2N: RJ2.P6 (MDI2-), U15.7 (MDIN2)
/ethernet 1/GM_MDI2P: RJ2.P5 (MDI2+), U15.6 (MDIP2)
/ethernet 1/GM_MDI3N: RJ2.P9 (MDI3-), U15.10 (MDIN3)
/ethernet 1/GM_MDI3P: RJ2.P8 (MDI3+), U15.9 (MDIP3)
/ethernet 1/GM_VDD10: C169.2, C170.2, C212.2, C214.2, L12.2, U15.3 (AVDD10), U15.8 (AVDD10), U15.21 (DVDD10), U15.38 (AVDD10)
/ethernet 1/GM_XTAL_IN: C216.2, U15.36 (XTAL_IN), X2.1
/ethernet 1/GM_XTAL_OUT: C218.2, U15.37 (XTAL_OUT/EXT_CLK), X2.3
/pcie&usb3/3.3Vaux: R203.2, U17.28 (B10_3.3Vaux)
/pcie&usb3/PCIE_B-RX0-DN: U16.12 (B1p), U17.17 (A17_HSI-)
/pcie&usb3/PCIE_B-RX0-DP: U16.11 (B1n), U17.16 (A16_HSI+)
/pcie&usb3/PCIE_B-TX0-DN: U16.14 (B0p), U17.33 (B15_HSO-)
/pcie&usb3/PCIE_B-TX0-DP: U16.13 (B0n), U17.32 (B14_HSO+)
/pcie&usb3/USB3-RX0-DN: U16.8 (C1p), USB4.8 (STDA_SSTX-)
/pcie&usb3/USB3-RX0-DP: U16.7 (C1n), USB4.9 (STDA_SSTX+)
/pcie&usb3/USB3-TX0-DN: U16.10 (C0p), USB4.5 (STDA_SSRX-)
/pcie&usb3/USB3-TX0-DP: U16.9 (C0n), USB4.6 (STDA_SSRX+)
/power input/CC1: D12.2, U1.A5 (CC1), U4.1 (CC1DB), U4.2 (CC1)
/power input/CC2: D14.2, U1.B5 (CC2), U4.4 (CC2), U4.5 (CC2DB)
/power input/DISCH: R161.1, U4.9 (DISCH)
/power input/PCIe_EN: Q3.3 (D), R185.2, U5.3 (EN)
/power input/POWER_OK3: Q3.1 (G), R184.2, U4.14 (POWER_OK3)
/power input/STUSB_SCL: J3.4, R163.2, U4.7 (SCL)
/power input/STUSB_SDA: J3.3, R164.2, U4.8 (SDA)
/power input/VBUS_DISCH: R157.1, U4.18 (VBUS_VS_DISCH)
/power input/VBUS_EN_SNK: R160.1, U4.16 (VBUS_EN_SNK)
/power input/VBUS_MAIN: C13.1, D1.1 (C), D15.2 (A), Q1.5 (D), Q1.6 (D), Q1.7 (D), Q1.8 (D), Q1.9 (D), R156.2, U1.A4B9 (VBUS), U1.B4A9 (VBUS), U4.24 (VDD)
/power input/VSYS: J3.1, R241.2, U4.22 (VSYS)
/power input/V_MAIN: C1.1, C9.1, C14.1, D3.1 (C), Q2.5 (D), Q2.6 (D), Q2.7 (D), Q2.8 (D), Q2.9 (D), R161.2, U3.2 (VIN), U3.3 (EN), U5.2 (VIN)
/power/SW_1: L4.2, U10.45 (SW_1), U10.46 (SW_2)
/usb/USB2.0-1_DN: D11.4 (IN3), D11.7 (NC), U22.11 (DM1), USB2.6 (D-)
/usb/USB2.0-1_DP: D11.5 (IN4), D11.6 (NC), U22.12 (DP1), USB2.7 (D+)
/usb/USB2.0-2_DN: D11.1 (IN1), D11.10 (NC), U22.9 (DM2), USB2.2 (D-)
/usb/USB2.0-2_DP: D11.2 (IN2), D11.9 (NC), U22.10 (DP2), USB2.3 (D+)
/usb/USB2.0-3_DN: D10.5 (IN4), D10.6 (NC), U22.8 (DP3), USB1.7 (D+)
/usb/USB2.0-3_DP: D10.4 (IN3), D10.7 (NC), U22.7 (DM3), USB1.6 (D-)
/usb/USB2.0-4_DN: D10.1 (IN1), D10.10 (NC), U22.5 (DM4), USB1.2 (D-)
/usb/USB2.0-4_DP: D10.2 (IN2), D10.9 (NC), U22.6 (DP4), USB1.3 (D+)
/wifi&bt/2.4G: C298.1, L13.1 (2.4GHz)
/wifi&bt/5.5G: C299.2, L13.4 (5.5GHz)
/wifi&bt/ANT0: L13.5 (Feed), L14.1, U19.2 (ANT0)
AGND: C337.1, C338.1, C339.1, C340.1, R232.1, U8.AA7 (GNDADC), U8.AE3 (AGND), U8.Y10 (VREFNADC)
ALDO1: C229.2, U10.13 (ALDO1)
ALDO2: C253.2, U10.14 (ALDO2)
ALDO3: C254.2, C421.2, U8.AE11 (VCC-PL), U10.16 (ALDO3)
ALDO4: C255.2, C337.2, C342.2, C425.2, C426.2, R207.1, R210.1, R212.2, R213.2, R214.2, R240.1, U8.AA9 (VREFPADC), U8.AB9 (AVCC), U8.AD15 (VCCDCXO), U8.AD25 (VDD18-DRAM), U8.AG15 (VCCPLL), U8.W7 (VCCADC), U10.17 (ALDO4)
ALDO-OUT: C332.2, U8.AE7 (ALDOOUT)
AP-NMI: C162.2, R231.2, U8.AM10 (NMI), U10.37 (IRQ)
AP-RESET: C163.2, R175.2, R230.2, SW2.1, U8.AJ11 (RESET), U10.1 (PWROK)
AUX-3V3: C159.2, C165.2, C167.2, C171.2, C177.2, C183.2, C184.2, C185.2, C205.2, C292.2, C293.2, C294.2, C302.2, C303.2, FPC1.22, FPC2.22, L2.2, R187.2, R201.1, R203.1, R215.1, R216.1, R217.1, R218.1, R219.1, R220.1, R221.1, R222.1, R223.1, R224.1, R225.1, R226.1, U13.22, U17.9 (A9_+3.3V), U17.10 (A10_+3.3V), U17.26 (B8_+3.3V), U24.22, U25.22, U26.22
BLDO1: C191.2, C192.2, C221.2, C415.2, C422.2, U8.AG9 (VCCPM), U8.T9 (VCC-PG), U10.18 (BLDO1), U19.22 (VIO)
BLDO2: C181.2, C187.2, C222.2, C308.2, C309.2, R176.2, U9.1 (EN), U10.19 (BLDO2), U12.F1 (VDD1), U12.F12 (VDD1), U12.G4 (VDD1), U12.G9 (VDD1), U12.T4 (VDD1), U12.T9 (VDD1), U12.U1 (VDD1), U12.U12 (VDD1)
BLDO3: C223.2, C333.2, C341.2, C351.2, C356.2, C359.2, C420.2, U8.AJ5 (CPVIN), U8.J15 (VCC18-PCIE), U8.K13 (VCCMCSI), U8.L22 (VCC18-EDP), U8.M21 (VCC18-HDMI), U10.21 (BLDO3)
BLDO4: C224.2, U10.22 (BLDO4)
CLDO1: C173.2, C228.2, C410.2, C412.2, C413.2, R204.1, R205.1, U2.8 (VCC), U8.N9 (VCCLVDS1), U8.N24 (VCCLVDS0), U8.U26 (VCC-PC), U10.23 (CLDO1)
CLDO2: C227.2, C423.2, U8.R26 (VCCEFUSE), U10.24 (CLDO2)
CLDO3: C226.2, C363.2, C407.2, C408.2, C428.2, U8.AC9 (VDD33), U8.J19 (VCC33-18-USB), U8.K19 (VCC33-USB), U8.L15 (VCC-IO), U10.26 (CLDO3/GPO0)
CLDO4: C225.2, U10.27 (CLDO4/GPO1)
CPUSLDO: C230.2, C405.2, C406.2, U8.AC15 (VDDCPUS), U10.28 (CPUSLDO)
CPVDD: C336.2, U8.AJ3 (CPVDD)
DCDC1: C233.2, C234.2, C377.2, C378.2, C379.2, C380.2, C381.2, C382.2, C383.2, C384.2, L5.2, U8.W19 (VDDCPUL), U8.W21 (VDDCPUL), U8.Y19 (VDDCPUL), U8.Y21 (VDDCPUL)
DCDC2: C235.2, C236.2, C348.2, C350.2, C352.2, C358.2, C360.2, C364.2, C385.2, C386.2, C387.2, C388.2, C389.2, C390.2, C391.2, C392.2, C393.2, C394.2, C395.2, C396.2, C397.2, C398.2, C427.2, L6.2, U8.J16 (VDD09-PCIE), U8.L18 (VDD09-USB), U8.L21 (VDD09-HDMI), U8.M22 (VDD09-EDP), U8.N13 (VDD-VE), U8.N21 (VDDDE), U8.P13 (VDD-VE), U8.P21 (VDDDE), U8.P22 (VDD-DE), U8.R15 (VDDSYS), U8.R17 (VDD-SYS), U8.R18 (VDD-SYS), U8.T11 (VDDGPU), U8.T13 (VDDGPU), U8.U12 (VDDGPU), U8.U13 (VDDGPU)
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
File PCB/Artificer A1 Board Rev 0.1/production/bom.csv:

Designator,Footprint,Quantity,Value,LCSC Part #
"C1, C14, C15",C_0805,3,10uF 50V,C440198
"C13, C3",C_0402,2,1uF 25V,C52923
"C133, C151, C154, C161, C309, C320, C321, C322, C323, C344, C345, C346, C347, C356, C358, C359, C360, C363, C364, C365, C375, C376, C383, C384, C392, C393, C398, C403, C406, C408, C410, C411, C412, C413, C414, C415, C416, C418, C419, C420, C421, C422, C423, C424, C426, C427, C428, C85, C86, C87, C88",0201,51,100nF 10V,
"C134, C135, C136, C137, C138, C139, C140, C141, C142, C143, C158, C159, C160, C164, C165, C167, C168, C170, C171, C172, C173, C174, C175, C176, C177, C178, C181, C183, C184, C185, C186, C187, C189, C191, C193, C199, C200, C207, C208, C211, C212, C213, C214, C300, C301",0201,45,100nF 16V,
"C16, C17, C2, C9",C_0402,4,100nF 50V,C307331
"C162, C163",0201,2,10nF 10V,
"C166, C169, C209, C210, C221, C222, C223, C224, C225, C226, C227, C228, C229, C230, C241, C253, C254, C255, C270, C271, C353",0201,21,2.2uF 10V,
"C179, C180, C292, C293, C294, C295, C296, C297",0603,8,22uF 16V,C2762594
C182,0201,1,22pF 16V,
"C188, C205, C291",0201,3,22pF 25V,
"C190, C192, C194, C219, C220, C231, C232, C247, C248, C249, C250, C251, C252, C257, C267, C272",0201,16,1uF 10V,
"C195, C197, C289",0201,3,3.3nF 16V,
"C196, C204, C290",0201,3,47pF 16V,
C198,0201,1,33pF 50V,
C201,0201,1,1nF 16V,
"C215, C216, C217, C218",0201,4,6pF 16V,
"C233, C234, C235, C236, C237, C238, C239, C240, C242, C261, C262, C263, C264, C265, C266, C268, C283, C284, C302, C303, C354, C377, C378, C385, C387, C389, C394, C399",0603,28,22uF 6.3V,C59461
"C243, C244, C245, C246, C256, C269, C273, C274, C275, C276, C277, C278, C324, C325, C326, C327",0402,16,10uF 6.3V,
"C25, C27",C_0805,2,22uF 25V,C45783
C258,0402,1,1uF 6.3V,
"C259, C260",0201,2,4pF 16V,
"C279, C280, C281",0402,3,4.7uF 6.3V,
"C282, C285, C286, C287, C288, C308, C310, C311, C312, C313, C314, C315, C316, C317, C318, C319, C328, C329, C330, C331, C332, C333, C334, C335, C336, C337, C341, C342, C348, C350, C351, C352, C379, C380, C381, C386, C388, C390, C391, C395, C396, C397, C400, C401, C402, C404, C405, C425",0201,48,2.2uF 6.3V,
C298,0201,1,6.2pF 16V,
C299,0201,1,0.4pF 16V,
"C304, C305, C306, C307",0201,4,12pF 16V,
"C338, C339, C340",0201,3,470nF 6.3V,
"C374, C382, C407, C409, C417",0201,5,1uF 6.3V,
CARD1,TF-SMD_TF-110,1,TF-110,C266613
CN2,CONN-TH_B2B-PH-K-S,1,B2B-PH-K-S,C131337
CN3,AUDIO-TH_PJ-393-8P,1,PJ-393-8P_C49284725,C49284725
"D1, D3",DFN1610-2L_L1.6-W1.0-P1.10-RD,2,ESDA25P35-1U1M-ES,C19170853
"D10, D11, D13, D4, D5, D6, D7, D8, D9",SLP2510P8_L2.5-W1.0-P0.50-BL,9,RClamp0524PATCT,C40960
"D12, D14",SOD-523_L1.2-W0.8-LS1.6-BI,2,LESD5D5.0CT1G_C5199850,C5199850
D15,SOD-523_L1.2-W0.8-LS1.6-RD,1,B5819WT_C7502714,C7502714
"D16, D17, D18",0402,3,GREEN LED,C74338
D2,0402,1,RED LED,C21260817
DP1,DP-SMD_CAR06-201EN5F,1,CAR06-201EN5F,C908454
"FPC1, FPC2",FPC-SMD_22P-P1.00_0.5K-A-22PB,2,0.5K-A-22PB,C2914146
HDMI1,HDMI-SMD_HD-A-05H9192N,1,HD-A-05H9191N,C18213861
J1,PinHeader_2x20_P2.54mm_Vertical,1,Conn_02x20_Odd_Even,C5224014
J2,PinHeader_1x02_P2.54mm_Vertical,1,Conn_01x02,C492401
J3,PinHeader_2x02_P1.27mm_Vertical,1,Conn_02x02_Odd_Even,C41370753
"L10, L3, L4, L5, L6, L7, L8, L9",IND-SMD_APH252012C3R3MP01,8,APH252012C1R0MP01,C42455356
"L11, L12",IND-SMD_L1.4-W1.2_AOTA-B141206SR47MT,2,APH141208C2R2MP01,C54123753
L13,ANT-SMD_6P-L1.6-W0.8-L,1,ANT162442DT-2001A2,C531339
L14,L0402,1,MLG1005S1N3BT000,C76767
L15,IND-SMD_L4.1-W4.1_MTQH404030S,1,10uH MTQH404030S100MBT,C51883185
"L16, L2",IND-SMD_L4.1-W4.1_MTQH404020S,2,3.3uH MTQH404020S3R3MBT,C51883183
"Q1, Q2",DFN-8_L3.0-W3.0-P0.65-BL,2,AON3419-TP,C49452346
"Q3, Q6, Q7",SOT-23,3,AO3401A,C15127
Q4,SOT-23-3_L2.9-W1.4-P1.90-LS2.6-BR,1,2SK3018,C727148
"R107, R108, R168, R176, R199, R202, R204, R205, R209, R212, R213, R214, R230, R231, R242",0201,15,10kΩ,
"R109, R110, R111, R158, R162, R163, R164, R165, R166, R169, R170, R171, R172, R174, R184, R185, R195, R198",0201,18,100kΩ,
"R112, R113",0201,2,2.49kΩ,
"R114, R115, R116, R117, R118, R119, R120, R121, R122, R123, R124, R125, R126, R127, R128, R129, R130, R131, R132, R133, R134, R135, R136, R137, R215, R216, R217, R218, R219, R220, R221, R222, R223, R224, R225, R226, R227, R228",0201,38,4.7kΩ,
"R144, R145, R146, R147, R156",0201,5,470Ω,
"R148, R149, R150, R154, R157, R161, R173, R196, R197, R233, R234",0201,11,1kΩ,
"R151, R152, R153",0201,3,200Ω,
R155,0201,1,39kΩ,
R159,0201,1,100Ω,
R160,0201,1,22kΩ,
"R167, R175, R229, R232, R237, R241",0201,6,0Ω,
R177,0201,1,120Ω,
"R178, R179",0201,2,240Ω,
R180,0201,1,18kΩ,
R181,0201,1,1.3kΩ,
"R182, R189, R190",0201,3,200kΩ,
"R183, R186, R191",0201,3,14kΩ,
R187,0201,1,75kΩ,
R188,0201,1,24kΩ,
R192,0201,1,27kΩ,
R193,0201,1,5.1kΩ,
R200,0402,1,10kΩ,
R203,0402,1,0Ω,
R206,0201,1,10MΩ,
R207,0201,1,4.3kΩ,
R208,0201,1,6.8kΩ,
R235,0201,1,2kΩ,
R236,0201,1,47kΩ,
"R238, R239",0201,2,22Ω,
R240,0201,1,1MΩ,
"R243, R244, R245",0201,3,33kΩ,
"RJ1, RJ2",RJ45-TH_HR911130A,2,HR911130A,C54408
"SW1, SW2",SW-SMD_4P-L3.5-W3.0-P1.50-LS4.7,2,TS-1185,C51927445
U1,USB-C-SMD_G-SWITCH_GT-USB-7010ASV,1,GT-USB-7010ASV,C2988369
U10,QFN-52_L6.0-W6.0-P0.40-TL-EP4.5,1,AXP717B,C45360051
U11,AXP323,1,AXP323,C45360050
U12,FBGA-200_L14.5-W10.0_RS1G32LF4D2BDS-53BT,1,K4UBE3D4AB-MGCL,C5827966
"U13, U24, U25, U26",FPC-SMD_22P-P1.00_AFC11-S22ICC-00,4,AFC11-S22ICA-00,C5248019
"U14, U15",WQFN-40_L5.0-W5.0-P0.4-BL-EP,2,RTL8211F-CG,C187932
U16,UQFN-16_L2.6-W1.8-P0.40-BL,1,HD3SS3202IRSVR,C2150836
U17,CONN-SMD_X3113WVS-36-9TV01,1,X1618WVS-36-9TV15,C21263102
U19,M8800DS2-40,1,~,
U2,WSON-8_L6.0-W5.0-P1.27-BL-EP,1,GD25LQ128EWIGR,C2928889
U21,SOT-23-6_L2.9-W1.6-P0.95-LS2.8-BL,1,CH217K,C83700
U22,QFN-24_L4.0-W4.0-P0.50-BL-EP2.8,1,CH334F_C5187527,C5187527
"U3, U6",SO-8_L4.9-W3.9-P1.27-LS6.0-BL-EP,2,AP64500SP-13,C2070920
U4,QFN-24_L4.0-W4.0-P0.50-BL-EP2.8,1,STUSB4500QTR,C2678061
U5,SO-8_L4.9-W3.9-P1.27-LS6.0-BL-EP,1,AP64350SP-13,C2071691
U8,BGA-664_L17.0-W17.0_T527,1,T527M00X0DCH,C28310420
U9,TSOT-23-5_L2.9-W1.6-P0.95-LS2.8-BR,1,SY8089A1AAC,C479074
"USB1, USB2",USB-A-TH_USB-M-51,2,Double layer DIP 90° black,C12049
USB4,USB-3.0-A-TH_HC-USB3.0-L168-WJ,1,HC-USB3.0-L168-WJ,C7501851
"X1, X2",Crystal_SMD_2520-4Pin_2.5x2.0mm,2,25MHz,C5265848
X3,CRYSTAL-SMD_4P-L3.2-W2.5-BL,1,SMD-3225_4P12M12PF10PPM,C133337
X4,Crystal_SMD_3225-4Pin_3.2x2.5mm,1,25MHz,C55155765
X5,OSC-SMD_L2.0-W1.2,1,SC-20S32.768kHz20PPM9pF,C97603
